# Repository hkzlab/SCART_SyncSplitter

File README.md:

# SCART Composite Sync Splitter/Cleaner

## Introduction

This card takes an RGB + Composite signal from a SCART connector and outputs the same RGB signal + split HSync/VSync (or CSync) on an 
HD15 (VGA) connector. This is **not** a scandoubler, and is meant to be used with multisync monitors that require either separated
sync signals or a clean csync.

The board is based around the LMH1981 IC and takes from 7 to 12VDC, center tip positive, as power input.

Currently tested with:

- Sony PlayStation 1 (PAL/50Hz)
- SEGA MegaDrive (PAL/60Hz mod)

Audio out is still **untested**.

You can order a PCB for this project [HERE](https://www.pcbway.com/project/shareproject/SCART_SyncSplitter_bdc49b8d.html).

### Disclaimer

I take NO responsibility for what happens if you decide to build and use this card. Your computer might crash, catch fire or be destroyed in other nasty ways.
You're encourauged to take what you deem fit from this, and use it in your projects!

### Sponsorship

This project is kindly sponsored by [PCBWay](https://pcbway.com).
PCBWay specializes in manufacturing high-quality PCBs and makes them affordable to hobbyist and professionals alike.

The range of services they offer include PCB prototyping, assembly, instant quotes for your order, a verification process by a team
of experts and an easy to use, hassle-free order process.

I'm grateful to PCBWay for the support in creating this project.

### 💰 Selling these boards 💰

I you want to contact me about selling this project, you can reach me via email at `0hkzUNDERSCOREprojects6ATposteoDOTnet` after properly fixing the email address by removing the digits and replacing the uppercase words with the proper characters.

**Contacts via other channels will be ignored**, as it means you did not read this document thoroughly.

"Collaborations" will boil down to the following:

- If you wish to produce and share this project at a loss or at cost, go for it. I am only asking for attribution and to let me know via email.
- If you want to do it for profit, let's discuss it. I'll probably settle for a rough 5% of the profit. Importing components is getting more expensive by the day, so this will contribute to me making future projects available for free.
- I will NOT do customer assistance for you or your customers. This is a hobby, not my job.

If this is not ok for you, you're cordially invited to go bother someone else :)

Authorized sellers will be listed in this README. If you find someone selling my boards without being listed here, it means they're stealing other people's work.

## Known Issues

### Rev. 0

- Pin 13 and 14 of the VGA connector (HSync and VSync) are swapped. Solved in Rev. 1

## Bill of Materials

| Component         | Qty | Type / Value           |
| ----------------- | --- | ---------------------- |
| C1                |  1  | 560pF / 1206 / ceramic |
| C2, C3, C4, C6    |  4  | 100nF / 1206 / ceramic |
| C5, C9            |  2  | 10uF radial e.l. caps  |
| C7                |  1  | 220nF / 1206 / ceramic |
| C8                |  1  | 4.7uF radial e.l. cap  |
| D1                |  1  | 1N400x THT diode       |
| D2                |  1  | led / 1206             |
| J1                |  1  | SCART female angled    |
| J2                |  1  | HD15 female, PCB mount |
| J3                |  1  | power jack connector   |
| J4                |  1  | 2x2 2.54mm headers     |
| J5                |  1  | stereo audio jack pcb  |
| JP1               |  1  | 1x2 2.54mm headers     |
| R1                |  1  | 75ohm / 1206           |
| R2, R4, R6, R8    |  4  | 100ohm / 1206          |
| R3                |  1  | 10k ohm 1% tol / 1206  |
| R10               |  1  | 470ohm / 1206          |
| U1                |  1  | LMH1981                |
| U2                |  1  | 7805 TO-263            |

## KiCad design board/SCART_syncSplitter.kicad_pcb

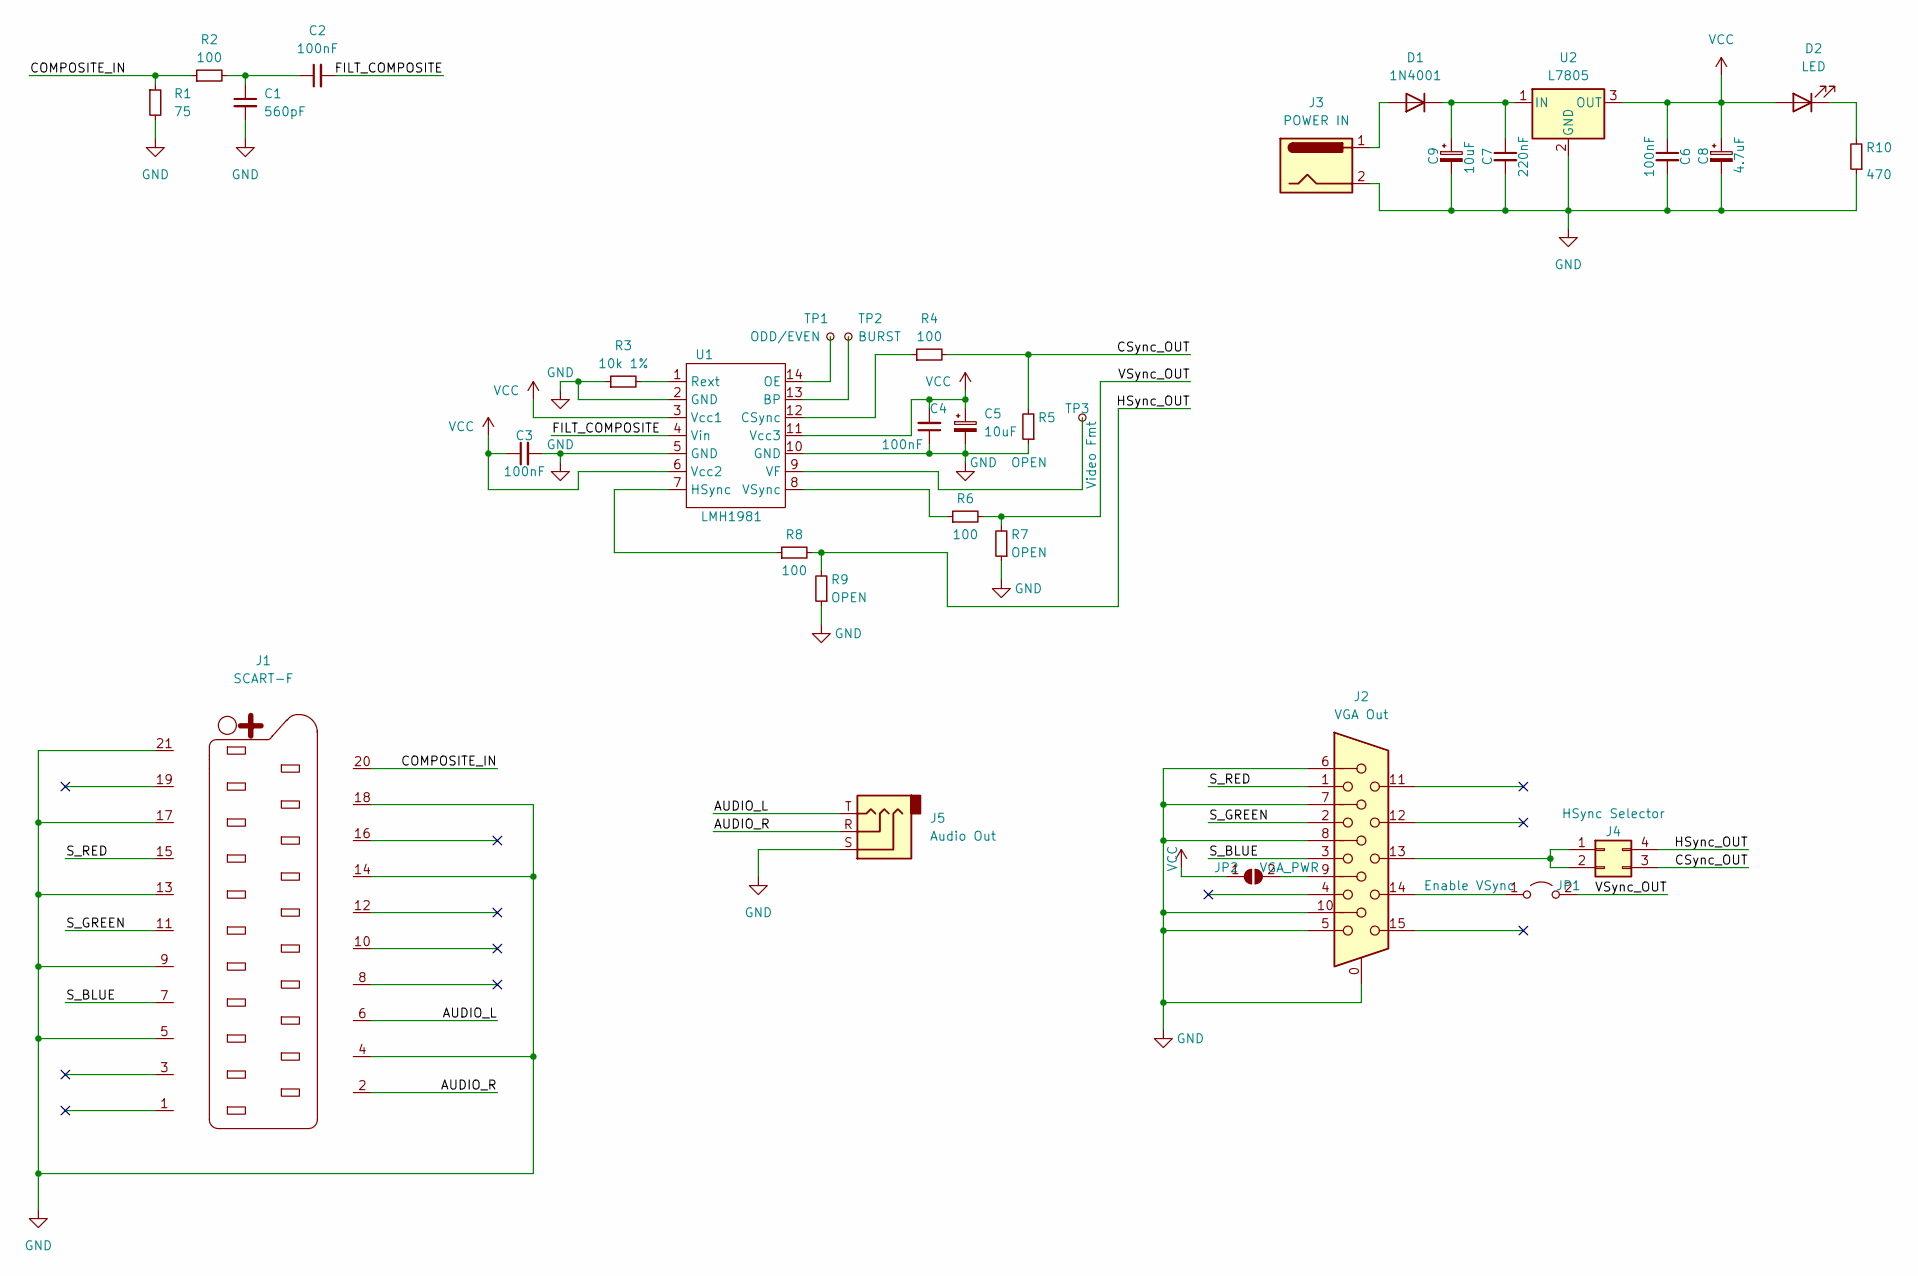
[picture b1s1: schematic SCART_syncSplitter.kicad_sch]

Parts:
C1: 560pF; C_1206_3216Metric_Pad1.33x1.80mm_HandSolder
C2, C3, C4, C6: 100nF; C_1206_3216Metric_Pad1.33x1.80mm_HandSolder
C5, C9: 10uF; CP_Radial_D5.0mm_P2.50mm
C7: 220nF; C_1206_3216Metric_Pad1.33x1.80mm_HandSolder
C8: 4.7uF; CP_Radial_D5.0mm_P2.50mm
D1: 1N4001; D_DO-41_SOD81_P10.16mm_Horizontal
D2: LED; LED_1206_3216Metric_Pad1.42x1.75mm_HandSolder
J1: SCART-F; SCART_F_RA
J2: VGA Out; DSUB-15-HD_Female_Horizontal_P2.29x1.98mm_EdgePinOffset3.03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
J3: POWER IN; BarrelJack_Horizontal
J4: HSync Selector; PinHeader_2x02_P2.54mm_Vertical
J5: Audio Out; Custom_3.5mm_jack
JP1: Enable VSync; PinHeader_1x02_P2.54mm_Vertical
JP2: VGA_PWR; SolderJumper-2_P1.3mm_Open_RoundedPad1.0x1.5mm
R1: 75; R_1206_3216Metric_Pad1.30x1.75mm_HandSolder
R2, R4, R6, R8: 100; R_1206_3216Metric_Pad1.30x1.75mm_HandSolder
R3: 10k 1%; R_1206_3216Metric_Pad1.30x1.75mm_HandSolder
R5, R7, R9: OPEN; R_1206_3216Metric_Pad1.30x1.75mm_HandSolder
R10: 470; R_1206_3216Metric_Pad1.30x1.75mm_HandSolder
TP1: ODD/EVEN; TestPoint_Pad_1.0x1.0mm
TP2: BURST; TestPoint_Pad_1.0x1.0mm
TP3: Video Fmt; TestPoint_Pad_1.0x1.0mm
U1: LMH1981; TSSOP-14_4.4x5mm_P0.65mm
U2: L7805; TO-263-3_TabPin2

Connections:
/AUDIO_L: J1.6, J5.T
/AUDIO_R: J1.2, J5.R
/COMPOSITE_IN: J1.20, R1.1, R2.1
/CSync_OUT: J4.3, R4.2, R5.2
/FILT_COMPOSITE: C2.2, U1.4 (Vin)
/HSync_OUT: J4.4, R8.2, R9.2
/S_BLUE: J1.7, J2.3
/S_GREEN: J1.11, J2.2
/S_RED: J1.15, J2.1
/VSync_OUT: JP1.2 (B), R6.2, R7.2
GND: C1.2, C3.2, C4.1, C5.2, C6.2, C7.2, C8.2, C9.2, J1.4, J1.5, J1.9, J1.13, J1.14, J1.17, J1.18, J1.21, J2.0, J2.5, J2.6, J2.7, J2.8, J2.10, J3.2, J5.S, R1.2, R3.1, R5.1, R7.1, R9.1, R10.1, U1.2 (GND), U1.5 (GND), U1.10 (GND), U2.2 (GND)
unnamed: C1.1, C2.1, R2.2
unnamed: D1.2 (A), J3.1
unnamed: C7.1, C9.1, D1.1 (K), U2.1 (IN)
unnamed: D2.1 (K), R10.2
unnamed: J2.13, J4.1, J4.2
unnamed: J2.14, JP1.1 (A)
unnamed: J2.9, JP2.2 (B)
unnamed: TP2.1, U1.13 (BP)
unnamed: R4.1, U1.12 (CSync)
unnamed: R8.1, U1.7 (HSync)
unnamed: TP1.1, U1.14 (OE)
unnamed: R3.2, U1.1 (Rext)
unnamed: TP3.1, U1.9 (VF)
unnamed: R6.1, U1.8 (VSync)
VCC: C3.1, C4.2, C5.1, C6.1, C8.1, D2.2 (A), JP2.1 (A), U1.3 (Vcc1), U1.6 (Vcc2), U1.11 (Vcc3), U2.3 (OUT)

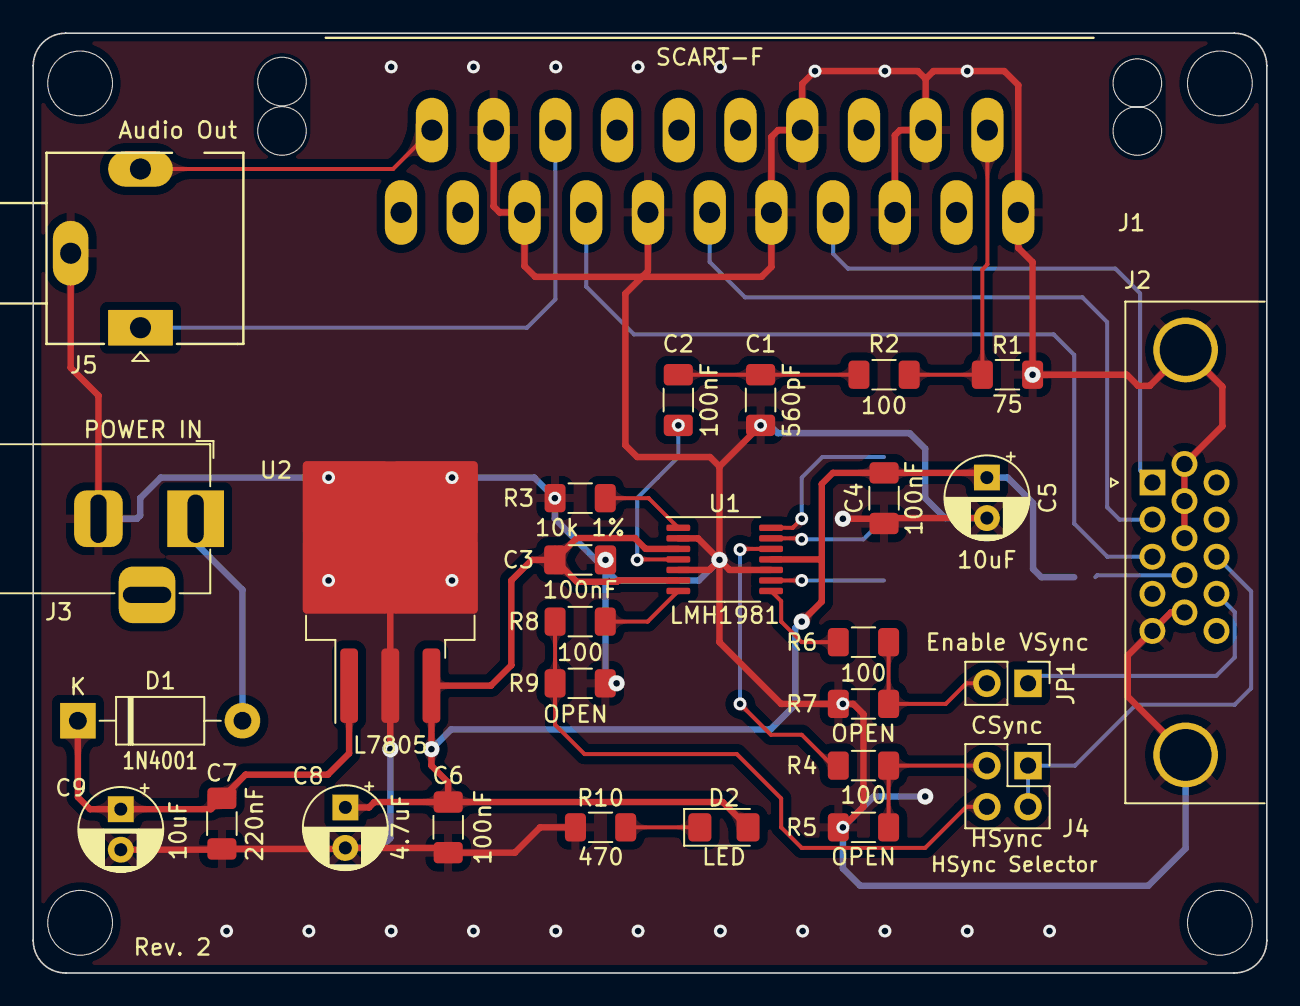
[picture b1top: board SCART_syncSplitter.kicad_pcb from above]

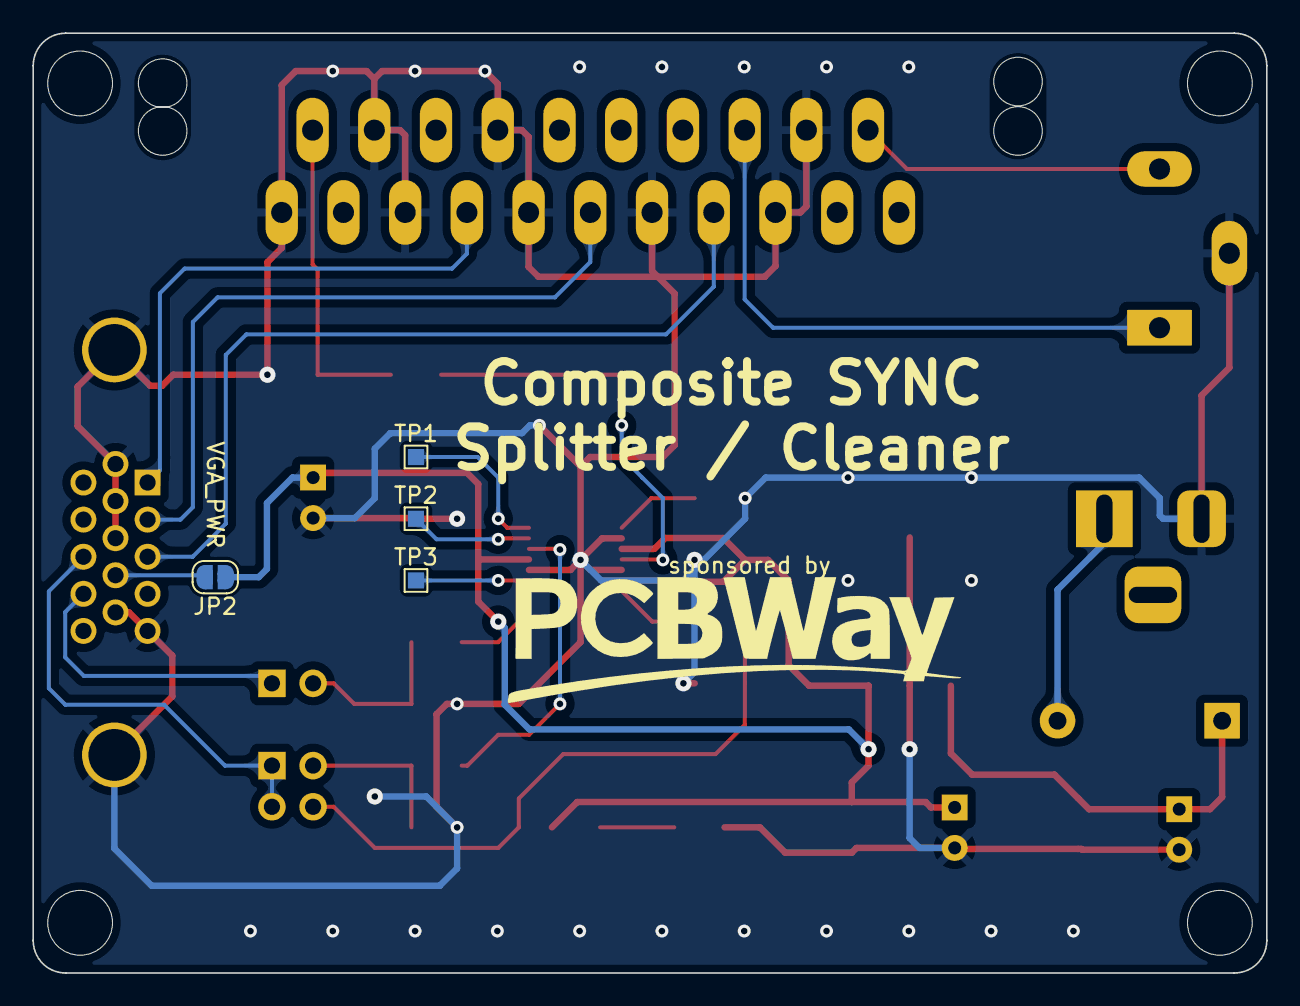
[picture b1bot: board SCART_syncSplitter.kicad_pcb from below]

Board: 2 copper layers, 76.1 x 58.0 mm, 33 parts (4 on the bottom side), 26 nets.

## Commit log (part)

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2023-10-18 Import and create required symbols
2023-10-22 Update the schematic
2023-10-22 Add VGA Out
2023-10-22 Added audio out
2023-10-23 Imported some libraries, started assigning footprints
2023-10-24 Assigned footprints
2023-10-24 Start preparing the PCB
2023-10-24 Add Power led
2023-10-24 Update the PCB
2023-10-24 Begin routing traces
2023-10-25 Drawn pcb
2023-10-26 Update PCB and schematic
2023-11-02 Added PCBWay logo
2023-11-02 Renamed directory
2023-11-02 Remove old gerbers
2023-11-02 Add schematics
2023-11-03 Update the README
2023-11-03 Added gerbers
2023-11-27 Change 570pF for C1 to 560
2023-12-01 Rev 1 of the schematics: invert vsync/hsync pins on VGA
2023-12-01 Update project for rev.1 board
2023-12-02 Further details
2024-01-05 Fix component quantity
2025-11-25 Prepare a rev.2 with mounting holes
2025-11-25 Reorganize some tracks
2025-11-25 Tweak some tracks
2025-11-25 Rework some tracks
2025-11-25 Add rev.2 board
2025-11-25 Update the PCB view
